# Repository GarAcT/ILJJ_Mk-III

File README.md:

# ILJJ Mk-III

コンパレータ付 8x8 CdSセル ダイナミックスキャン回路

## 仕様

3入力/8出力。
入力はスキャンを行う列 (2進数指定)、出力は半固定抵抗によって設定されたしきい値と比較した結果。

基板にはCdSセルは実装せず、外部にダイオードと共に回路図通りに配線されているものとし、基板の8ピンソケット2つと接続する。

ユニバーサル基板用の設計。

## 経緯

木更津高専情報工学科2年 実験実習II 文化祭での展示へ向けたボードゲーム制作

対戦型ペントミノを作ることになり、置かれたピースの判定にセンシングが必要になり制作した基板。
8x8に並べられたCdSセルをスキャンし、事前に設定したしきい値と比較して各マスにピースが置かれたか判定する。

ちなみにこれを稼働させるソフトウェアは [Joくん](https://github.com/nuller-jo) が担当。

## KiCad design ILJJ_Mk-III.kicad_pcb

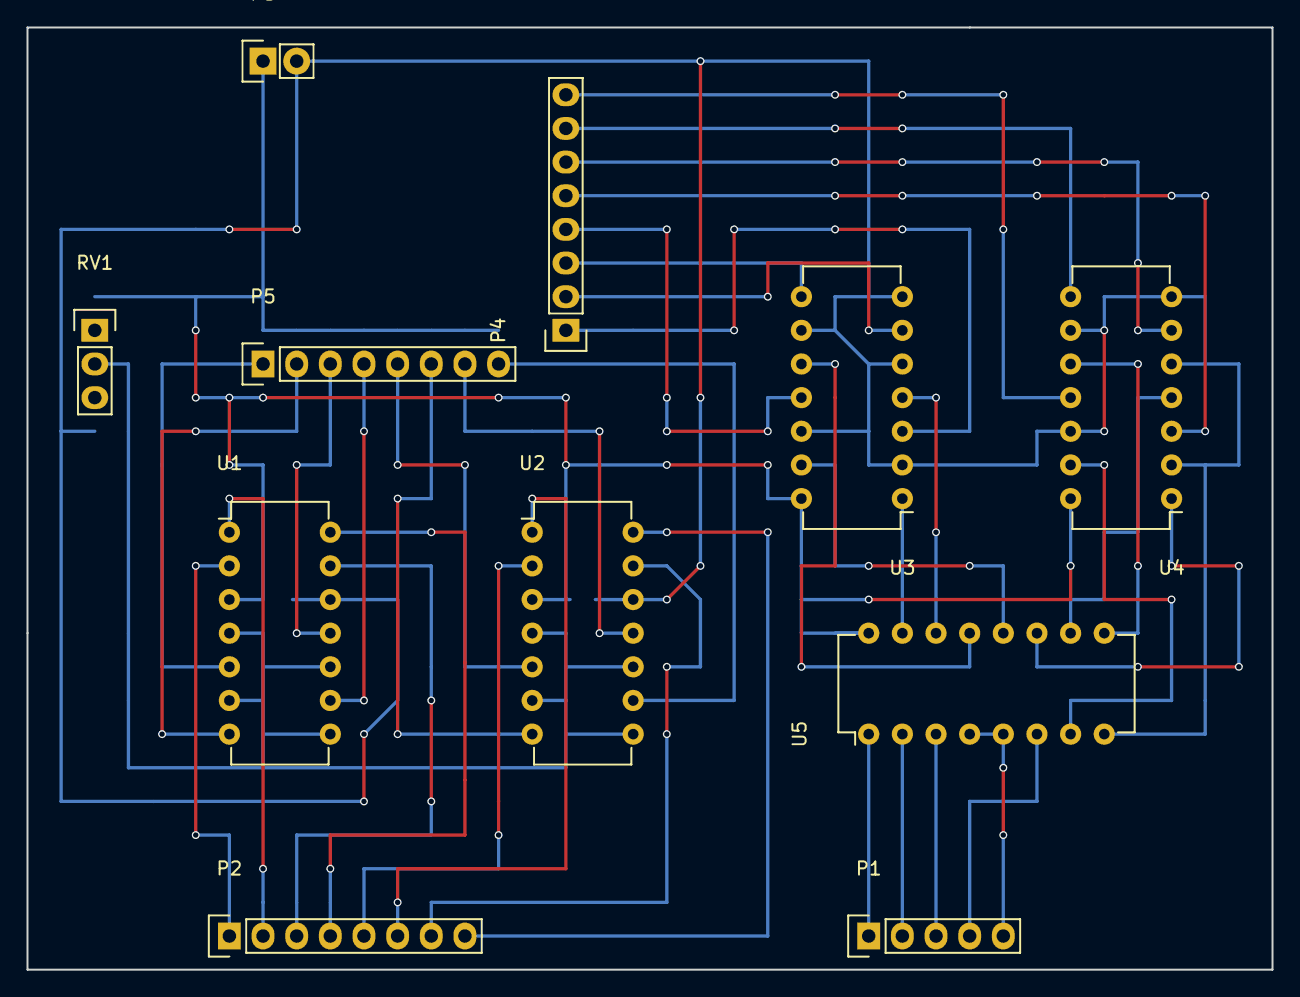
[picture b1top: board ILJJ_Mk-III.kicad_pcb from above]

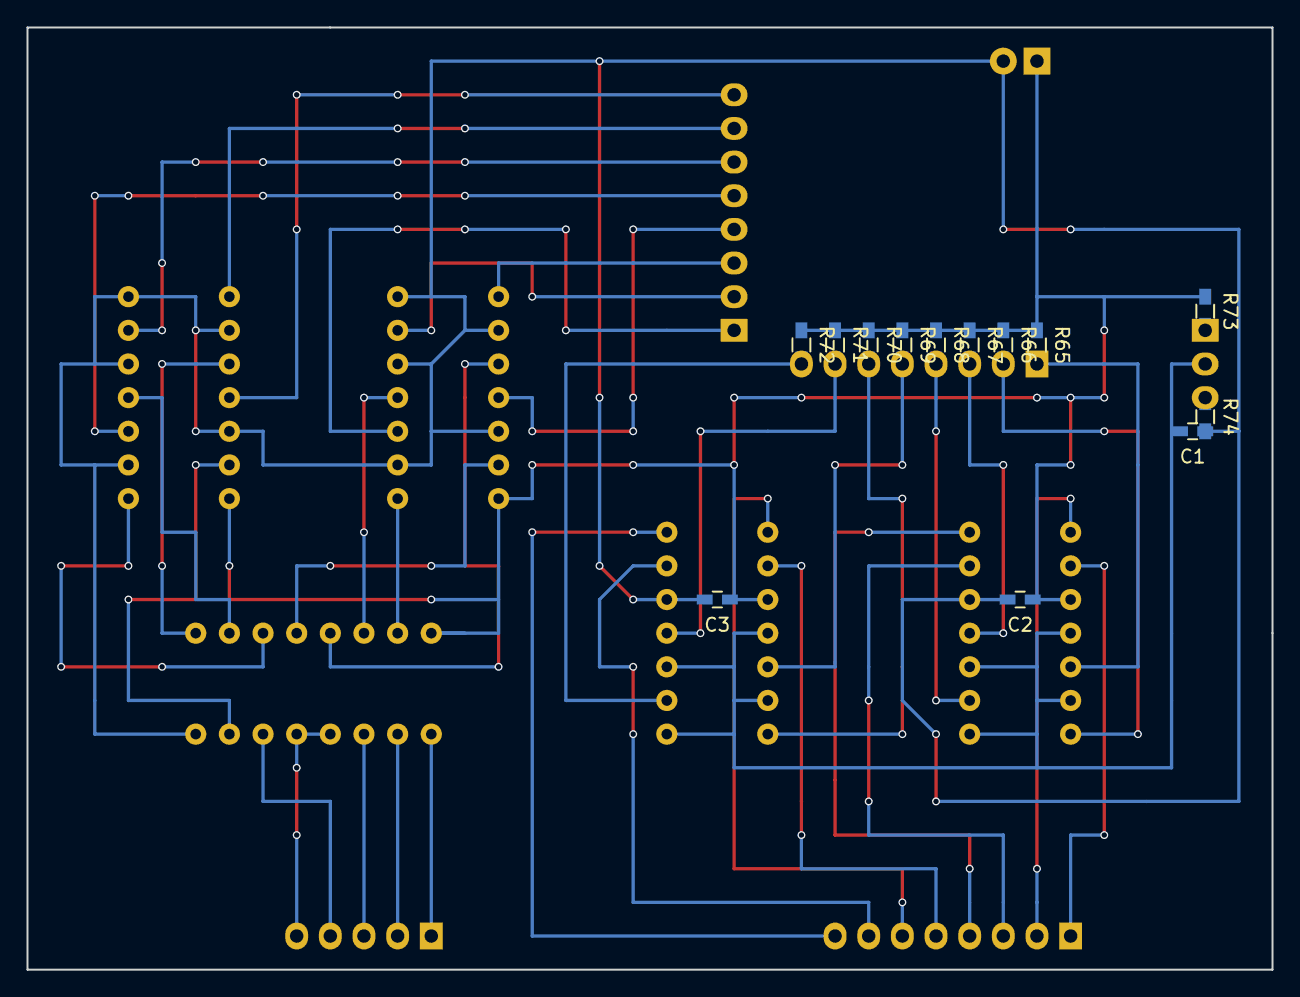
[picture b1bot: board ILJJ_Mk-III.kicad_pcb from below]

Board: 2 copper layers, 94.0 x 71.1 mm, 24 parts (13 on the bottom side), 42 nets.

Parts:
C1: 0.1uF; C_0603_HandSoldering
C2, C3: C; C_0603_HandSoldering
P1: CONN_01X05; Socket_Strip_Straight_1x05
P2, P4, P5: CONN_01X08; Socket_Strip_Straight_1x08
P3: CONN_01X02; Socket_Strip_Straight_1x02
R65, R66, R67, R68, R69, R70, R71, R72, R73, R74: R; R_0603_HandSoldering
RV1: POT; Pin_Header_Straight_1x03
U1, U2: LM339; DIP-14_W7.62mm
U3, U4: 74LS125; DIP-14_W7.62mm
U5: 74LS238; DIP-16_W7.62mm

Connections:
GND: C1.1, C2.2, C3.2, P3.2, R74.2, U1.12, U2.12, U3.2, U3.5, U3.7, U3.9, U3.12, U4.2, U4.5, U4.7, U4.9, U4.12, U5.8
unnamed: C1.2, RV1.2, U1.4, U1.6, U1.8, U1.10, U2.4, U2.6, U2.8, U2.10
unnamed: P1.1, U5.1
unnamed: P1.2, U5.2
unnamed: P1.3, U5.3
unnamed: P1.4, U5.6
unnamed: P1.5, U5.4, U5.5
unnamed: P2.1, U1.2
unnamed: P2.2, U1.1
unnamed: P2.3, U1.13
unnamed: P2.4, U1.14
unnamed: P2.5, U2.2
unnamed: P2.6, U2.1
unnamed: P2.7, U2.13
unnamed: P2.8, U2.14
unnamed: P4.1, U3.3
unnamed: P4.2, U3.6
unnamed: P4.3, U3.8
unnamed: P4.4, U3.11
unnamed: P4.5, U4.3
unnamed: P4.6, U4.6
unnamed: P4.7, U4.8
unnamed: P4.8, U4.11
unnamed: P5.1, R65.2, U1.5
unnamed: P5.2, R66.2, U1.7
unnamed: P5.3, R67.2, U1.11
unnamed: P5.4, R68.2, U1.9
unnamed: P5.5, R69.2, U2.5
unnamed: P5.6, R70.2, U2.7
unnamed: P5.7, R71.2, U2.11
unnamed: P5.8, R72.2, U2.9
unnamed: R73.2, RV1.1
unnamed: R74.1, RV1.3
unnamed: U3.1, U5.15
unnamed: U3.4, U5.14
unnamed: U3.10, U5.13
unnamed: U3.13, U5.12
unnamed: U4.1, U5.11
unnamed: U4.4, U5.10
unnamed: U4.10, U5.9
unnamed: U4.13, U5.7
VCC: C2.1, C3.1, P3.1, R65.1, R66.1, R67.1, R68.1, R69.1, R70.1, R71.1, R72.1, R73.1, U1.3, U2.3, U3.14, U4.14, U5.16

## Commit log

2018-06-19 [add] README.md
